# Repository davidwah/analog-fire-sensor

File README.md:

# Fire Sensor

1. Top View  

3. Bottom View

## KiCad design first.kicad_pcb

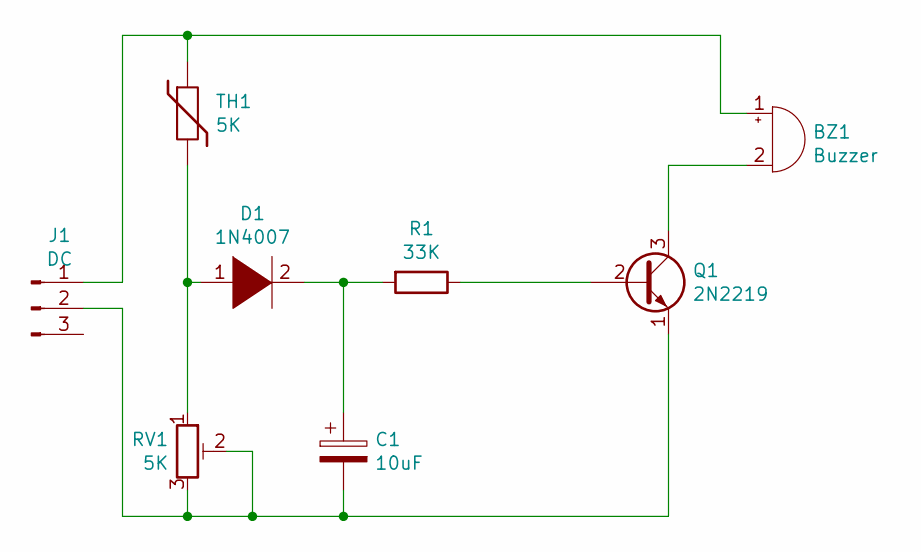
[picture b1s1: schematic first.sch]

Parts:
BZ1: Buzzer; Buzzer_12x9.5RM7.6
C1: 10uF; CP_Radial_D10.0mm_P3.50mm
D1: 1N4007; D_5W_P10.16mm_Horizontal
J1: DC; PinHeader_1x03_P2.54mm_Vertical
Q1: 2N2219; TO-39-3
R1: 33K; R_Axial_DIN0411_L9.9mm_D3.6mm_P12.70mm_Horizontal
RV1: 5K; Potentiometer_ACP_CA6-H2,5_Horizontal
TH1: 5K; PinHeader_1x02_P1.27mm_Vertical

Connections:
unnamed: BZ1.1 (-), J1.1, TH1.1
unnamed: BZ1.2 (+), Q1.3 (C)
unnamed: C1.1, D1.2 (A), R1.2
unnamed: C1.2, J1.2, Q1.1 (E), RV1.2, RV1.3
unnamed: D1.1 (K), RV1.1, TH1.2
unnamed: Q1.2 (B), R1.1

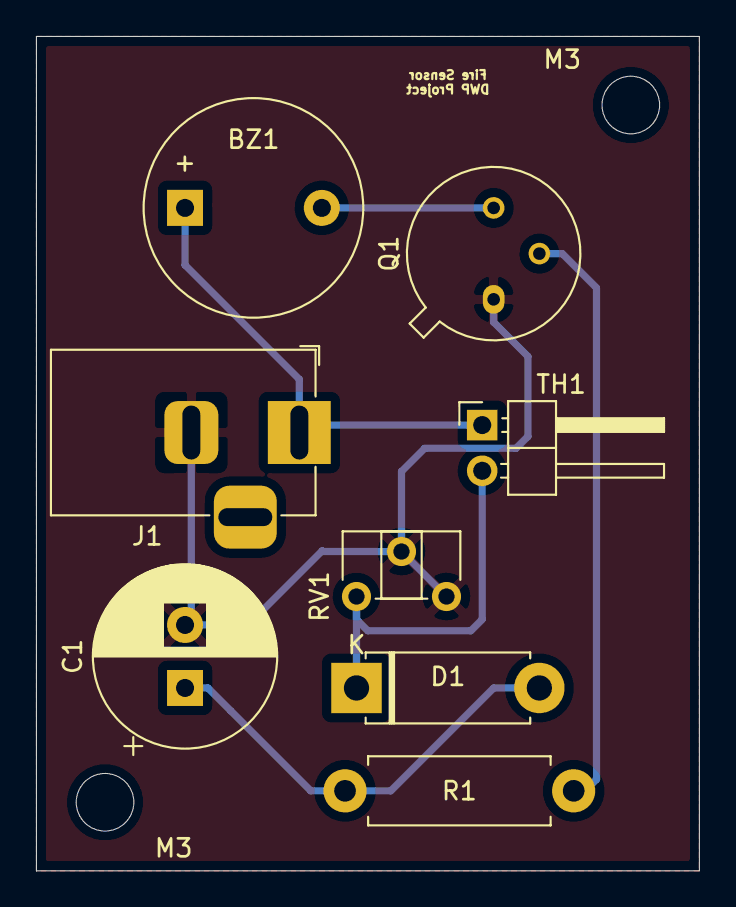
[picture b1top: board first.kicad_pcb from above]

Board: 2 copper layers, 36.8 x 46.4 mm, 10 parts (0 on the bottom side), 6 nets.

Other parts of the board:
M3, M3#2: MountingHole_3.2mm_M3

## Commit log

2021-10-26 add Kicad fire-sensor
2021-10-26 add gerber file
2021-10-26 add images
